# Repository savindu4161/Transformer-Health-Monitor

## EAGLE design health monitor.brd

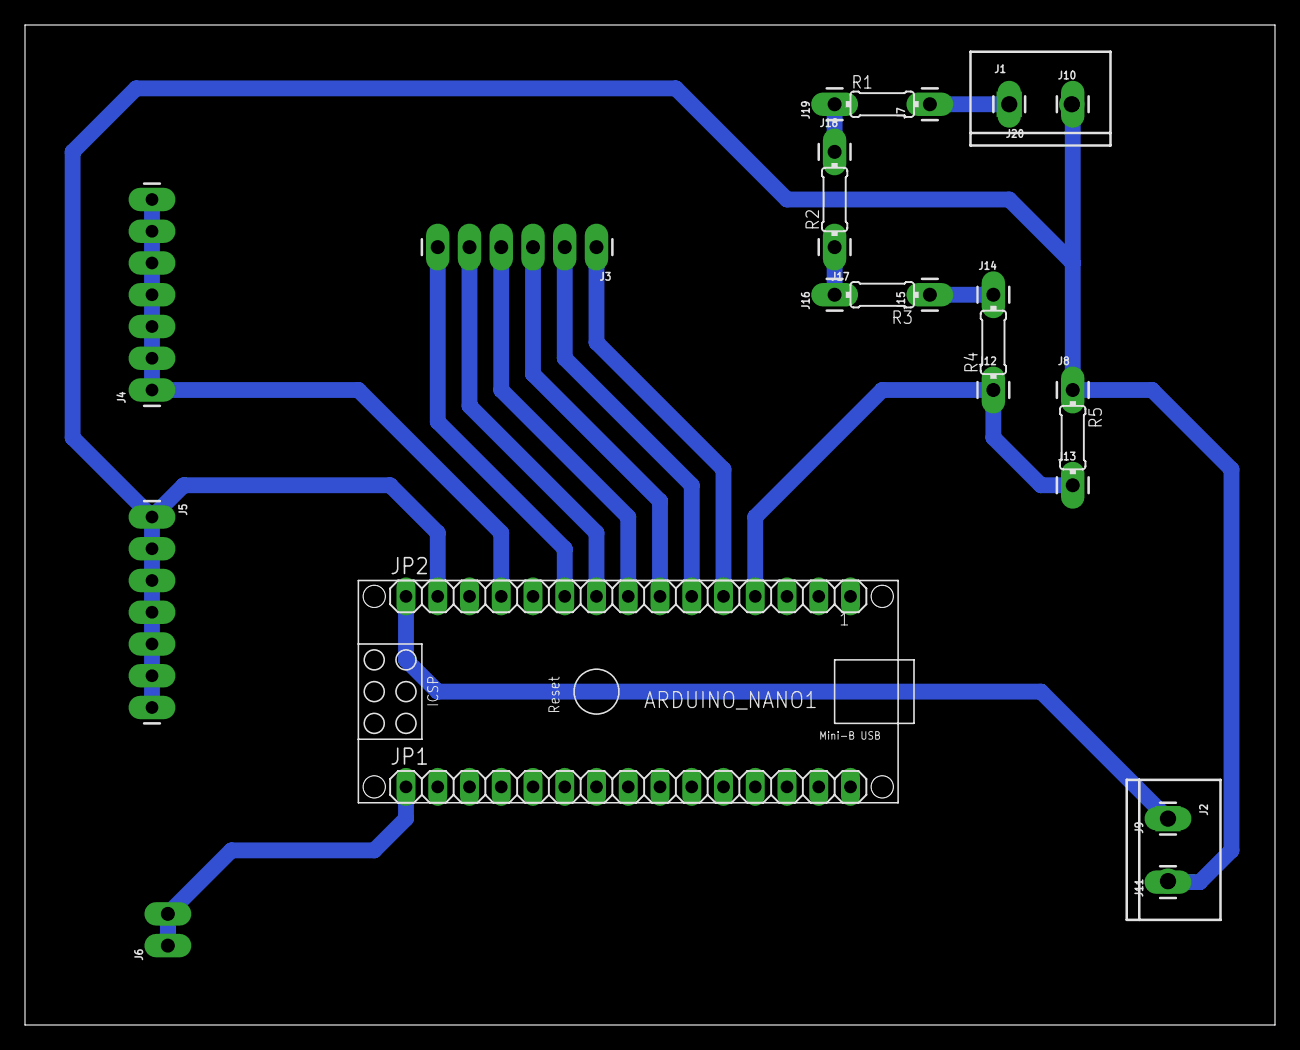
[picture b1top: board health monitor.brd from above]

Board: 2 copper layers, 100.0 x 80.0 mm, 28 parts (0 on the bottom side), 20 nets.

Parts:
ARDUINO_NANO1: ARDUINO_NANO
J1, J2: SCREWTERMINAL-5MM-2
J3: 1X06_LONGPADS
J4, J5: 1X07_LONGPADS
J6: 1X02_LONGPADS
J7, J8, J9, J10, J11, J12, J13, J14, J15, J16, J17, J18, J19, J20: 1X01_LONGPAD
JP1, JP2: 1X15
R1, R2, R3, R4, R5: 0204/7

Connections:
unnamed: ARDUINO_NANO1.13, JP2.3
unnamed: ARDUINO_NANO1.12, J4.1, J4.2, J4.3, J4.4, J4.5, J4.6, J4.7, JP2.4
unnamed: ARDUINO_NANO1.11, JP2.5
unnamed: ARDUINO_NANO1.3, JP2.13
unnamed: ARDUINO_NANO1.2, JP2.14
unnamed: ARDUINO_NANO1.1, JP2.15
unnamed: ARDUINO_NANO1.16, J6.1, J6.2
unnamed: ARDUINO_NANO1.15, J2.1, J9.1, JP2.1
unnamed: J1.1, J7.1, J20.1, R1.2
unnamed: ARDUINO_NANO1.10, J3.6, JP2.6
unnamed: ARDUINO_NANO1.9, J3.5, JP2.7
unnamed: ARDUINO_NANO1.8, J3.4, JP2.8
unnamed: ARDUINO_NANO1.7, J3.3, JP2.9
unnamed: ARDUINO_NANO1.6, J3.2, JP2.10
unnamed: ARDUINO_NANO1.5, J3.1, JP2.11
unnamed: J16.1, J17.1, R2.1, R3.2
unnamed: J18.1, J19.1, R1.1, R2.2
unnamed: ARDUINO_NANO1.14, J1.2, J2.2, J5.1, J5.2, J5.3, J5.4, J5.5, J5.6, J5.7, J8.1, J10.1, J11.1, JP2.2, R5.1
unnamed: ARDUINO_NANO1.4, J12.1, J13.1, JP2.12, R4.1, R5.2
unnamed: J14.1, J15.1, R3.1, R4.2

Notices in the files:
parts and their libraries:
SparkFun-Connectors: Licensing: Creative Commons ShareAlike 4.0 International - https://creativecommons.org/licenses/by-sa/4.0
